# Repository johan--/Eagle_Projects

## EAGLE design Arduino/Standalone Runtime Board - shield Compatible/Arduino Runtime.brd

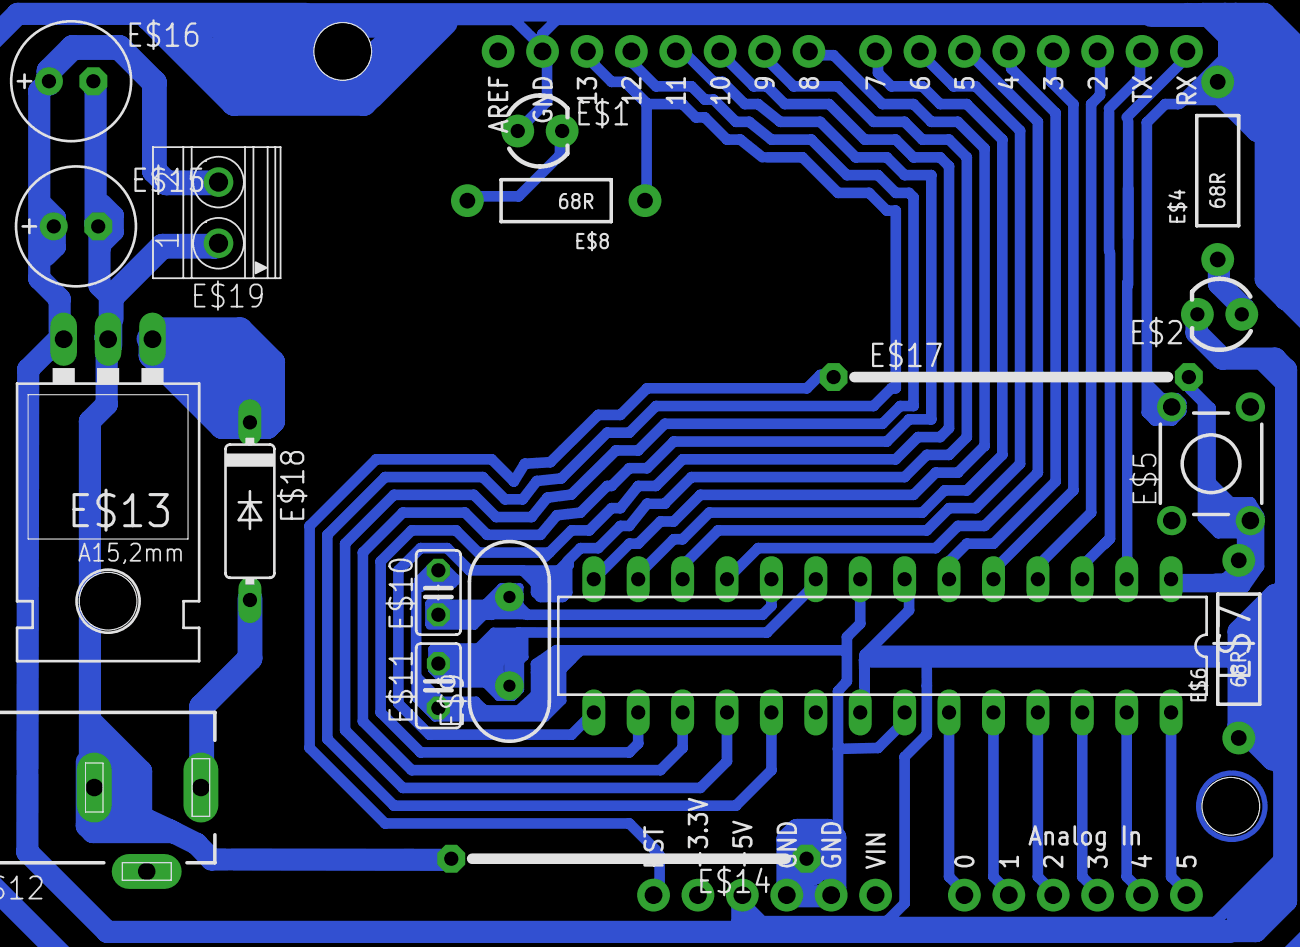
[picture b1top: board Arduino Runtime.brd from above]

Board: 2 copper layers, 19 parts (0 on the bottom side), 2 nets.

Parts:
E$1, E$2: LED3MM
E$3: DUEMILANOVE_SHIELD
E$4, E$6, E$8: 68R; AXIAL-0.4
E$5: TL1105
E$7: ATMEGAxx8; DIL28-3
E$9: 16Mhz; HC49US
E$10, E$11: 22p; C025-025X050
E$12: DCJ0303
E$13: 78XXL
E$14, E$17: 20
E$15, E$16: E2,5-7
E$18: C5102
E$19: 1751248

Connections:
S$104: E$7.10, E$9.2
S$105: E$7.9, E$9.1

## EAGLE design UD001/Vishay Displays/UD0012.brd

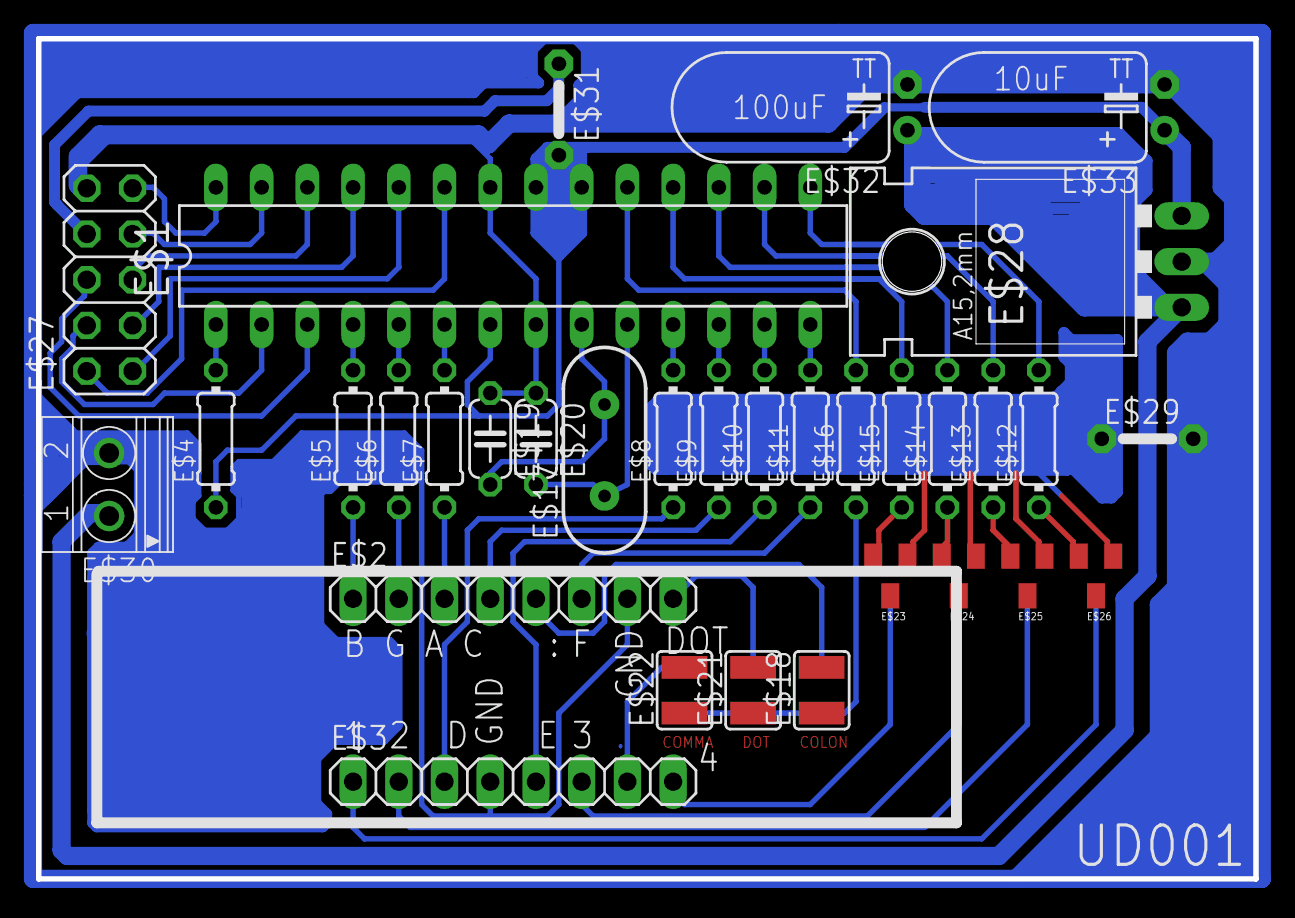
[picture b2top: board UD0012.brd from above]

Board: 2 copper layers, 67.6 x 46.7 mm, 33 parts (0 on the bottom side), 20 nets.

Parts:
E$1: DIL28-3
E$2, E$3: 1X08
E$4, E$5, E$6, E$7, E$8, E$9, E$10, E$11, E$12, E$13, E$14, E$15, E$16: 0204/7
E$17: HC49US
E$18, E$21, E$22: SJW
E$19, E$20: C050-024X044
E$23, E$24, E$25, E$26: SOT23
E$27: 2X05
E$28: 78XXL
E$29, E$31: 05
E$30: 1751248
E$32, E$33: TT2D6L

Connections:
S$1: E$1.1, E$4.2
S$2: E$1.4, E$5.2
S$3: E$1.5, E$6.2
S$4: E$1.6, E$7.2
S$5: E$1.11, E$8.2
S$6: E$1.12, E$9.2
S$7: E$1.13, E$10.2
S$8: E$1.14, E$11.2
S$10: E$1.10, E$17.1, E$20.2
S$31: E$2.1, E$5.1
S$33: E$2.3, E$7.1
S$34: E$3.3, E$8.1
S$35: E$2.4, E$9.1
S$36: E$3.5, E$10.1
S$37: E$2.6, E$11.1
S$46: E$1.7, E$1.20, E$1.21, E$28.OUT
S$57: E$28.IN, E$32.+
S$59: E$1.9, E$17.2, E$19.2
S$74: E$2.7, E$3.4
S$89: E$1.8, E$1.22, E$19.1, E$20.1

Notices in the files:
parts and their libraries:
SparkFun-Passives: Licensing: CC v3.0 Share-Alike You are welcome to use this library for commercial purposes.
